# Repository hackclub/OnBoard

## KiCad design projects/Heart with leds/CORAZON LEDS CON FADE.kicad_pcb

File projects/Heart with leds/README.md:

---
name: "Franco Gonzalez Liotta"
slack_handle: "@Franco"
github_handle: "@aGuyWhoHasGithub"
tutorial: # None
---

# Heart with leds(ajustable fade in and fade out frequency and brightness)

<!-- Describe your board in 2-3 sentences. What are you making? What will it do? -->
This  project is basically a heart-shaped form pcb with leds that turn on-off with fade in and fade out effect,
which you can adjust, also the brightness is adjustable.

<!-- How much is it going to cost? -->
10.89 reais of the cost of 5 pcbs(since its cheaper than paying the order with dollars) and 147.97 reais of shipping cost
<!-- Tell us a little bit about your design process. What were some challenges? What helped? ***Totally optional*** -->
Nothing was that complicated, it was very easy for me to be honest...

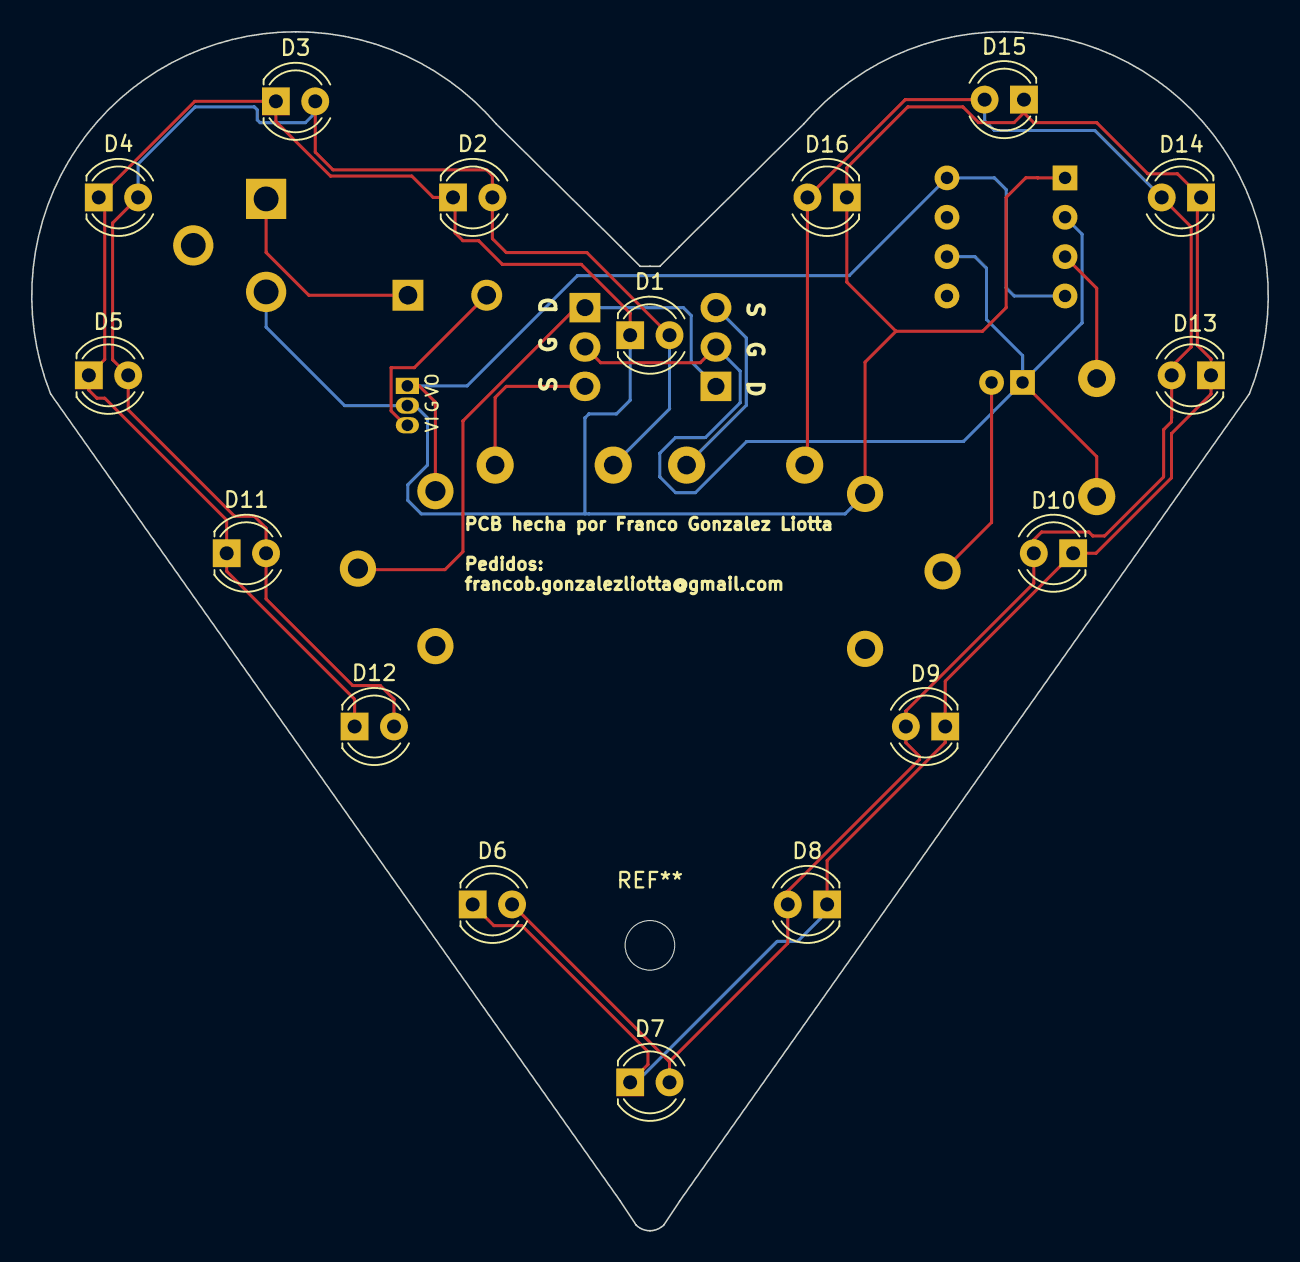
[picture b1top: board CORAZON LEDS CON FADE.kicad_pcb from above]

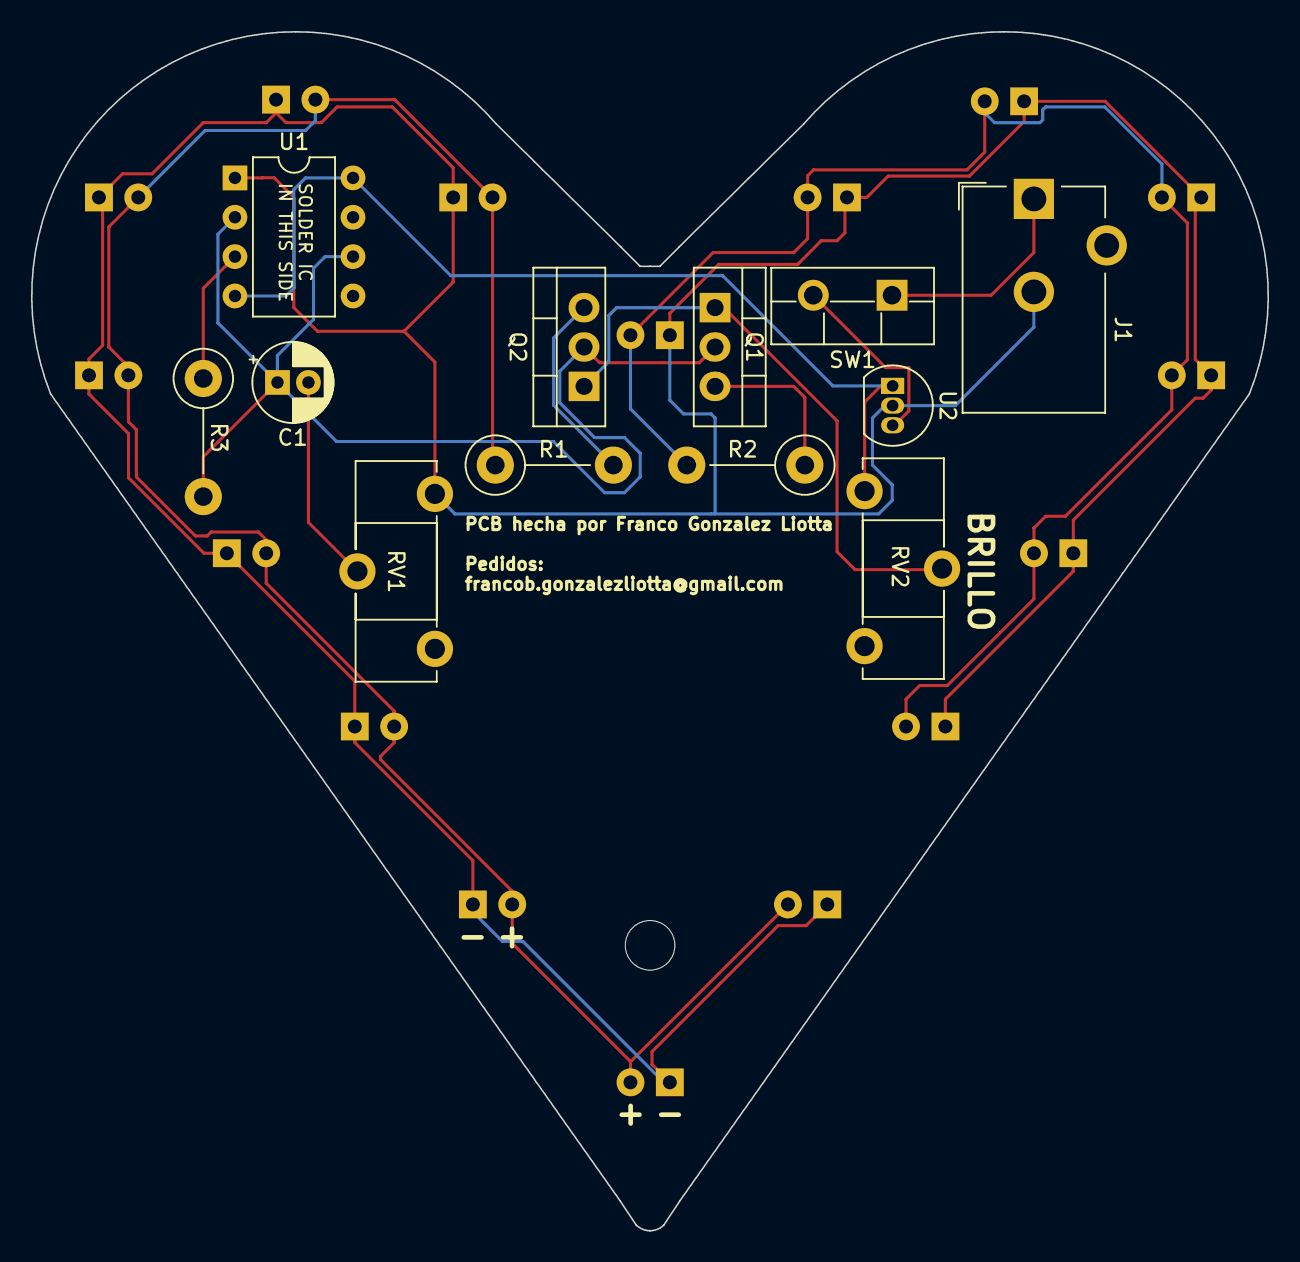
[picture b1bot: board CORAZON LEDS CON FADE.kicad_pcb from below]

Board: 2 copper layers, 79.8 x 77.4 mm, 28 parts (12 on the bottom side), 5 nets.

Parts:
C1: C_Polarized; CP_Radial_D5.0mm_P2.00mm
D1, D2, D3, D4, D5, D6, D7, D8, D9, D10, D11, D12, D13, D14, D15, D16: LED; LED_D4.0mm
J1: Jack-DC; BarrelJack_CUI_PJ-102AH_Horizontal
Q1, Q2: NMOS; TO-220-3_Vertical
R1, R2, R3: R; R_Axial_DIN0411_L9.9mm_D3.6mm_P7.62mm_Vertical
RV1, RV2: R_Potentiometer; Potentiometer_ACP_CA14-H5_Horizontal
SW1: SW_SPST; TO-220F-2_Vertical
U1: NE555P; DIP-8_W7.62mm
U2: L78L05_TO92; TO-92_Inline

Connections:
NET-(J1-VI): J1.1, SW1.1 (A)
unnamed: D1.2 (A), D2.2 (A), D3.2 (A), D4.2 (A), D5.2 (A), D11.2 (A), D12.2 (A), R2.2
unnamed: D6.2 (A), D7.2 (A), D8.2 (A), D9.2 (A), D10.2 (A), D13.2 (A), D14.2 (A), D15.2 (A), D16.2 (A), R1.1
unnamed: SW1.2 (B), U2.3 (VI)
unnamed: RV2.1, U1.4 (R), U1.8 (VCC), U2.1 (VO)

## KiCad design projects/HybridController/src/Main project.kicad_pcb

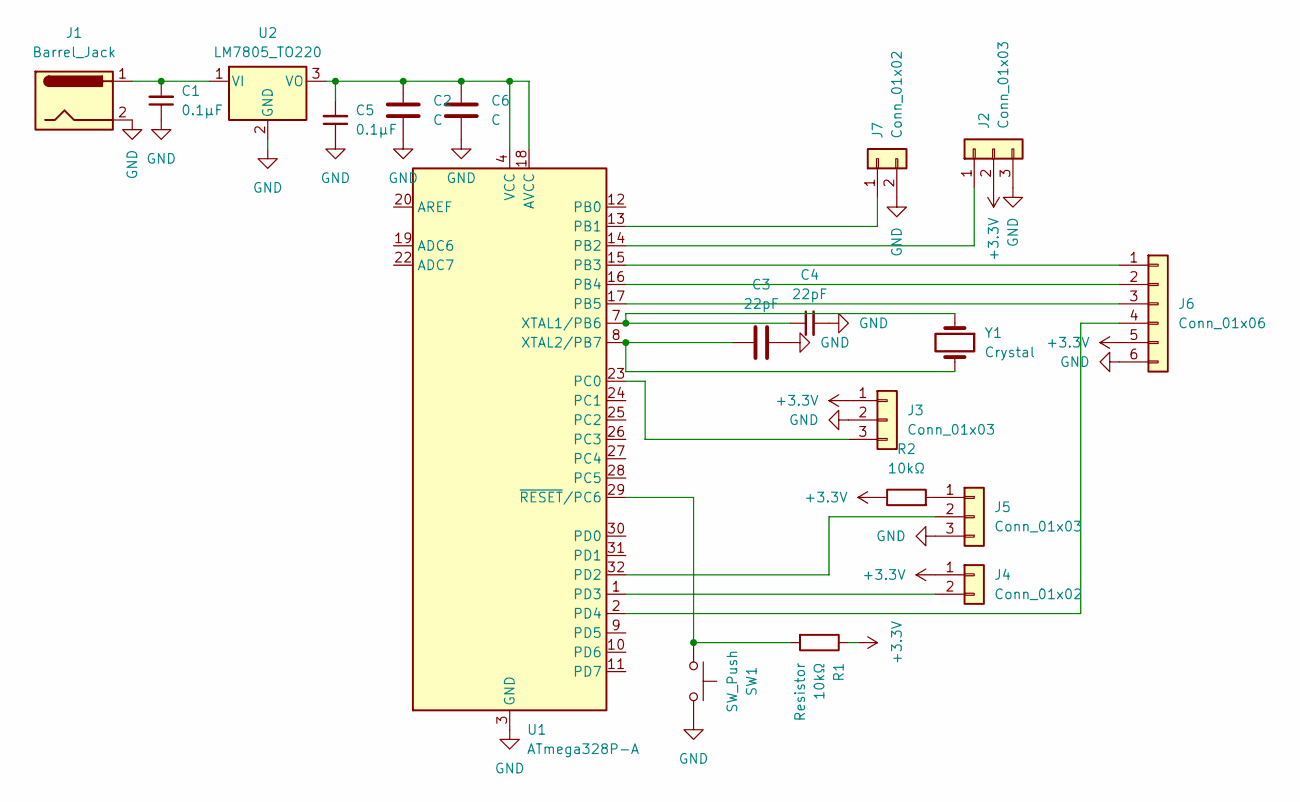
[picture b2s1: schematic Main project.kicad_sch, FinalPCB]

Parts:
C1, C5: 0.1µF; C_0805_2012Metric
C2, C6: C; C_0805_2012Metric
C3, C4: 22pF; C_0805_2012Metric
J1: Barrel_Jack; BarrelJack_SwitchcraftConxall_RAPC10U_Horizontal
J2, J3, J5: Conn_01x03; PinHeader_1x03_P2.54mm_Vertical
J4, J7: Conn_01x02; PinHeader_1x02_P2.54mm_Vertical
J6: Conn_01x06; PinHeader_1x06_P2.54mm_Vertical
R1: 10kΩ; C_0805_2012Metric
R2: 10kΩ; R_0805_2012Metric
SW1: SW_Push; SW_Push_1P1T_NO_6x6mm_H9.5mm
U1: ATmega328P-A; TQFP-32_7x7mm_P0.8mm
U2: LM7805_TO220; TO-220-3_Vertical
Y1: Crystal; Crystal_HC49-U_Vertical

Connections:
+3.3V: J2.2, J3.1, J4.1, J6.5, R1.1, R2.1
GND: C1.1, C2.1, C3.2, C4.2, C5.1, C6.1, J1.2, J2.3, J3.2, J5.3, J6.6, J7.2, SW1.2, U1.3 (GND), U1.5 (GND), U1.21 (GND), U2.2 (GND)
unnamed: J2.1, U1.14 (PB2)
unnamed: J3.3, U1.23 (PC0)
unnamed: J4.2, U1.1 (PD3)
unnamed: J5.1, R2.2
unnamed: J5.2, U1.32 (PD2)
unnamed: J6.1, U1.15 (PB3)
unnamed: J6.2, U1.16 (PB4)
unnamed: J6.3, U1.17 (PB5)
unnamed: J6.4, U1.2 (PD4)
unnamed: J7.1, U1.13 (PB1)
unnamed: C2.2, C5.2, C6.2, U1.4 (VCC), U1.6 (VCC), U1.18 (AVCC), U2.3 (VO)
unnamed: C4.1, U1.7 (XTAL1/PB6), Y1.1
unnamed: C3.1, U1.8 (XTAL2/PB7), Y1.2
unnamed: R1.2, SW1.1, U1.29 (~RESET/PC6)
unnamed: C1.2, J1.1, U2.1 (VI)

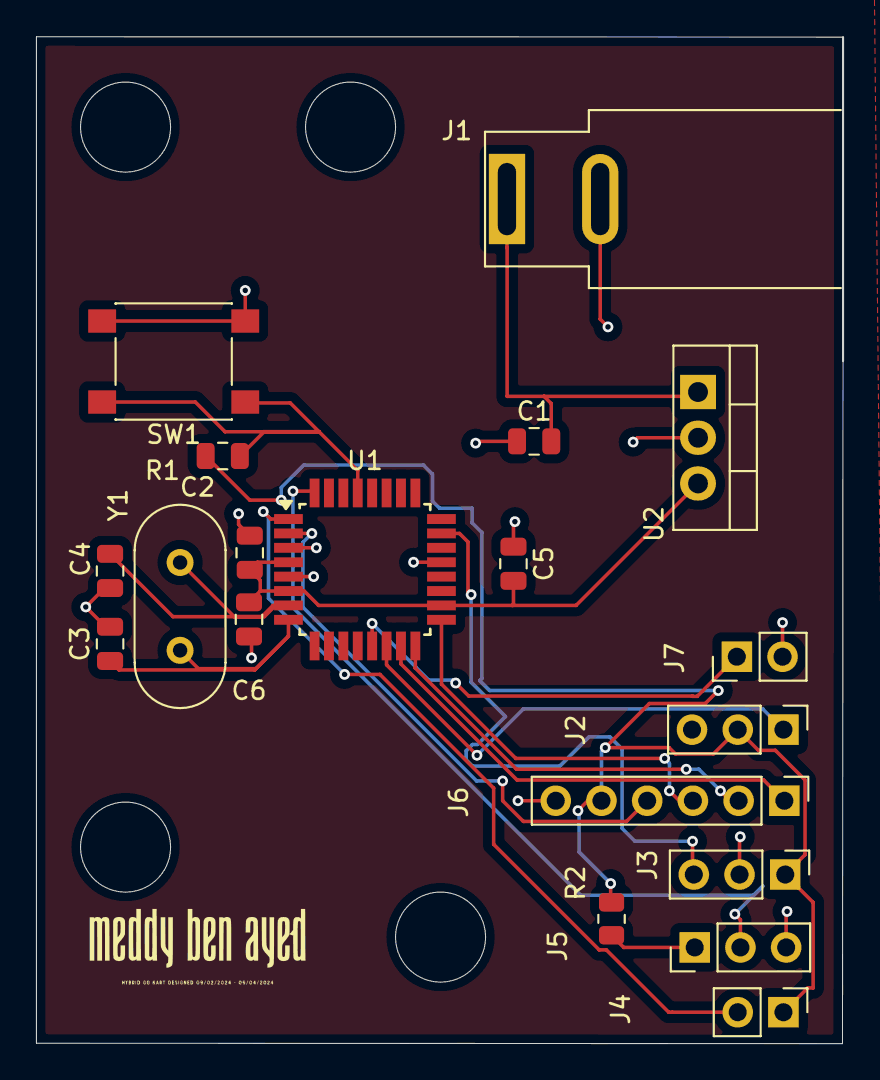
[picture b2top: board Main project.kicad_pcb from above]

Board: 4 copper layers, 44.8 x 55.9 mm, 20 parts (0 on the bottom side), 17 nets.

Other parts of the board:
 : logo

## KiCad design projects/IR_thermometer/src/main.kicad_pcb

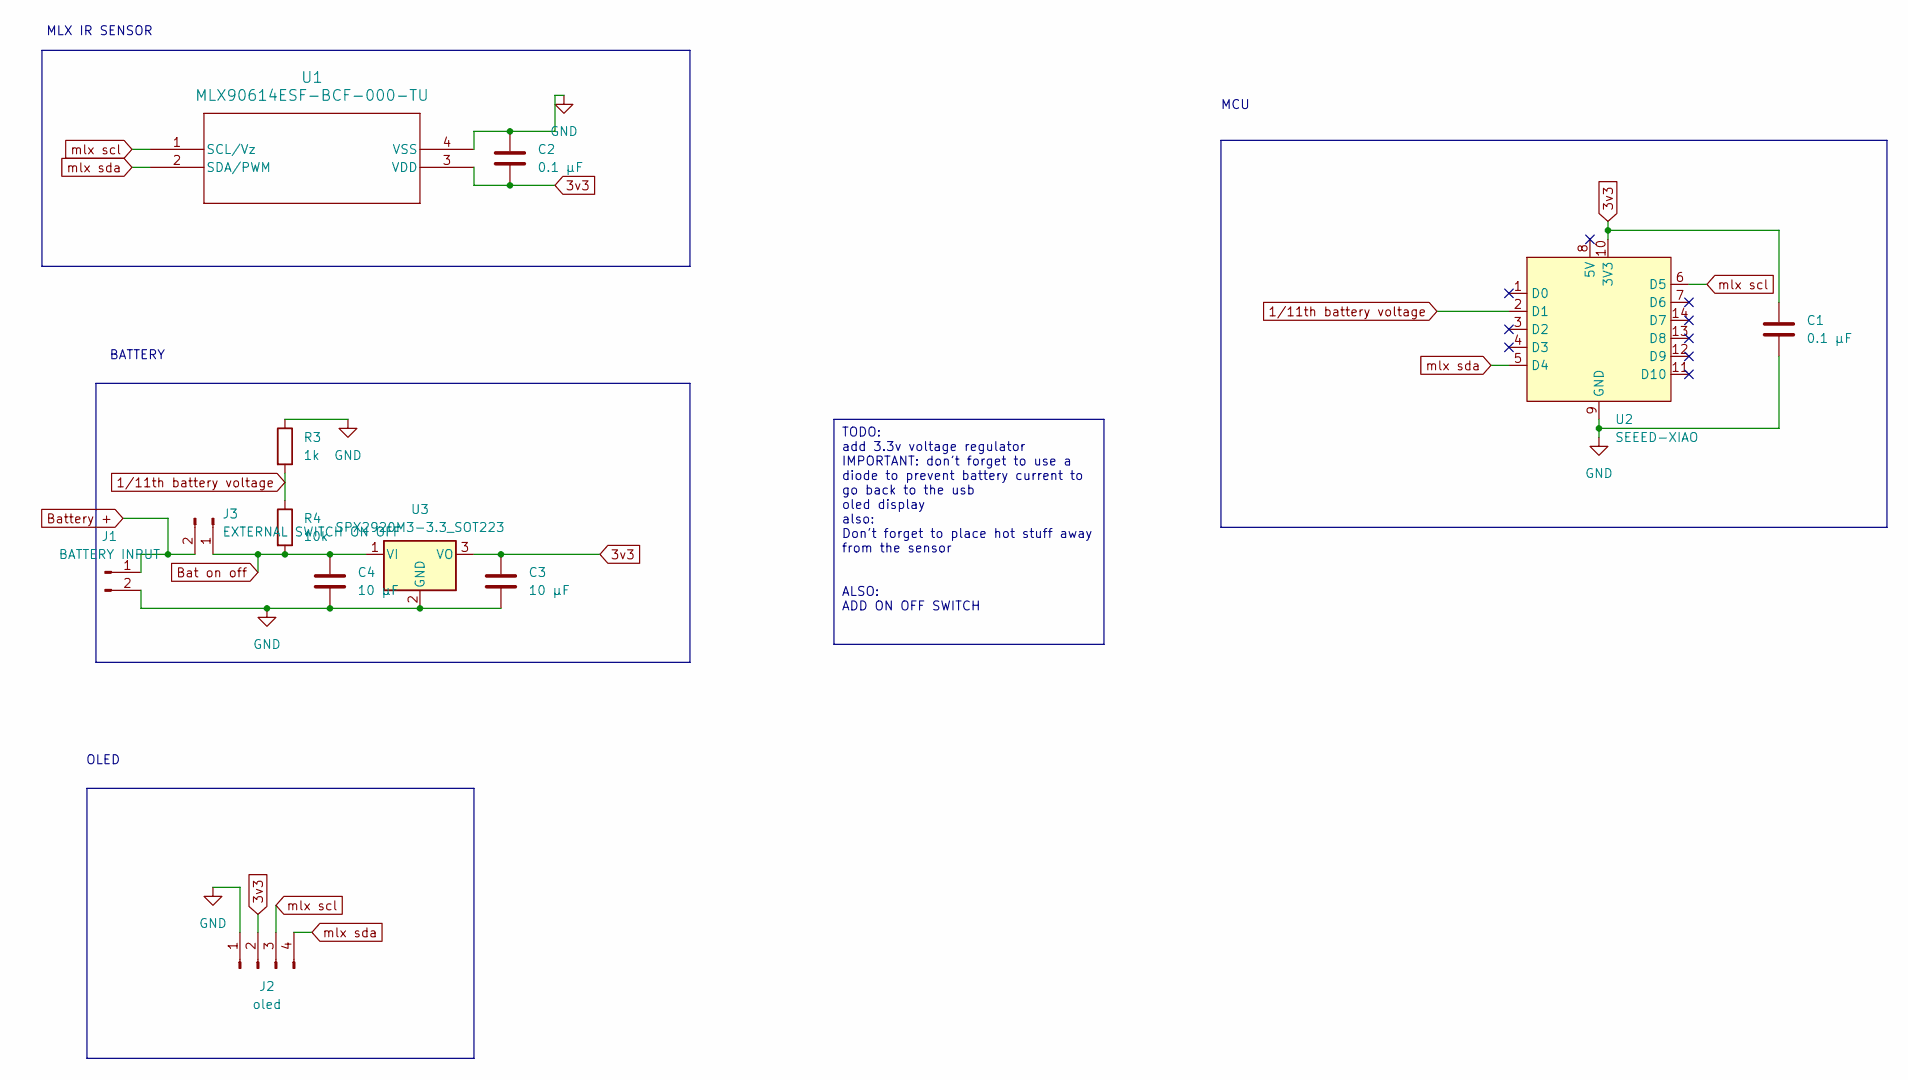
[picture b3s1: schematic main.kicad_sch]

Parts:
C1, C2: 0.1 µF; C_0805_2012Metric_Pad1.18x1.45mm_HandSolder
C3, C4: 10 µF; C_0805_2012Metric_Pad1.18x1.45mm_HandSolder
J1: BATTERY INPUT; PinHeader_1x02_P2.54mm_Vertical
J2: oled; PinHeader_1x04_P2.54mm_Vertical
J3: EXTERNAL SWITCH ON OFF; PinHeader_1x02_P2.54mm_Vertical
R3: 1k; R_0805_2012Metric_Pad1.20x1.40mm_HandSolder
R4: 10k; R_0805_2012Metric_Pad1.20x1.40mm_HandSolder
U1: MLX90614ESF-BCF-000-TU; MLX90614xCF_MEL
U2: SEEED-XIAO; XIAO-14P-THT-2.54-21x17.8MM
U3: SPX2920M3-3.3_SOT223; SOT-223-3_TabPin2

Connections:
1/11th battery voltage: R3.2, R4.1, U2.2 (D1)
3v3: C1.1, C2.2, C3.1, J2.2, U1.3 (VDD), U2.10 (3V3), U3.3 (VO)
Bat on off: C4.1, J3.1, R4.2, U3.1 (VI)
Battery +: J1.1, J3.2
GND: C1.2, C2.1, C3.2, C4.2, J1.2, J2.1, R3.1, U1.4 (VSS), U2.9 (GND), U3.2 (GND)
mlx scl: J2.3, U1.1 (SCL/Vz), U2.6 (D5)
mlx sda: J2.4, U1.2 (SDA/PWM), U2.5 (D4)

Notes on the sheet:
TODO: add 3.3v voltage regulator IMPORTANT: don't forget to use a diode to prevent battery current to go back to the usb oled display also: Don't forget to place hot stuff away from the sensor ALSO: ADD ON OFF SWITCH
MLX IR SENSOR
BATTERY
OLED
MCU

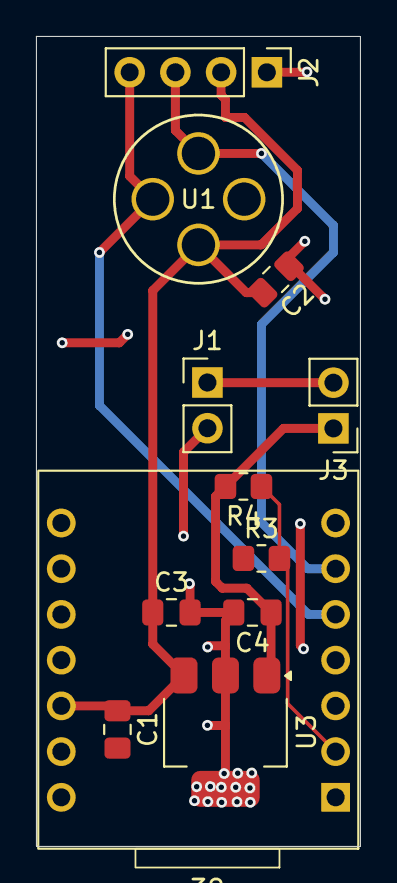
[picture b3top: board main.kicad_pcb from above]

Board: 2 copper layers, 18.0 x 45.0 mm, 12 parts (0 on the bottom side), 7 nets.

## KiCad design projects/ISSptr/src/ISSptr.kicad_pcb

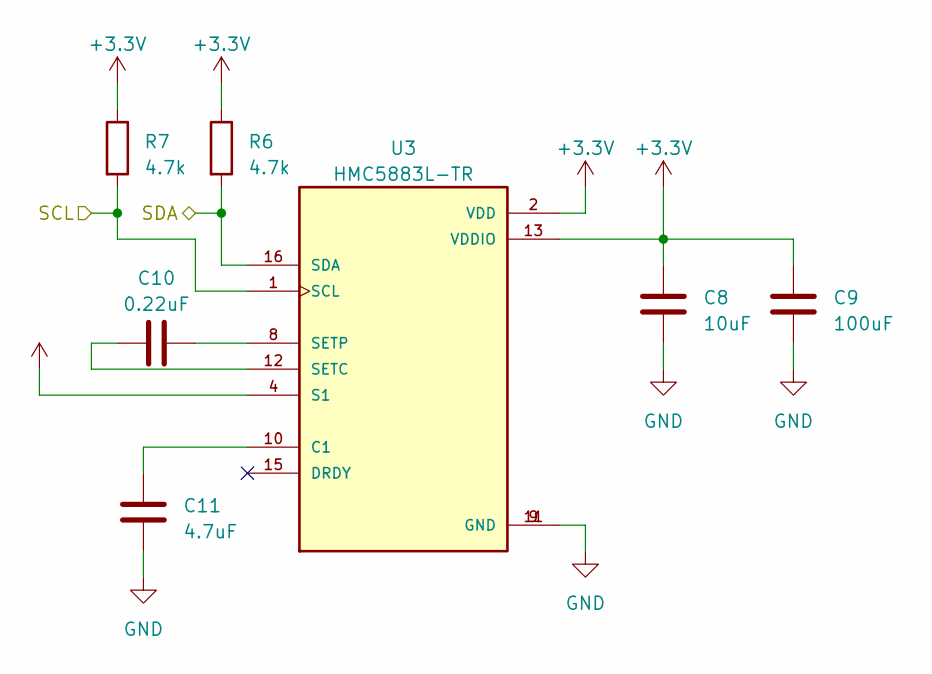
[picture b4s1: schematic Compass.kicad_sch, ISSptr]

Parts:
C8: 10uF; C_0603_1608Metric; LCSC C19702
C9: 100uF; C_0603_1608Metric; LCSC C730416
C10: 0.22uF; C_0603_1608Metric; LCSC C472764
C11: 4.7uF; C_0603_1608Metric; LCSC C307469
R6, R7: 4.7k; R_0603_1608Metric; LCSC C23162
U3: HMC5883L-TR; XDCR_HMC5883L-TR; PARTREV E; LCSC C976032

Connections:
+3.3V: C8.1, C9.1, R6.1, R7.1, U3.2 (VDD), U3.4 (S1), U3.13 (VDDIO); also elsewhere on the board
/Compass/SCL: R7.2, U3.1 (SCL); also elsewhere on the board
/Compass/SDA: R6.2, U3.16 (SDA); also elsewhere on the board
GND: C8.2, C9.2, C11.1, U3.9 (GND), U3.11 (GND); also elsewhere on the board
unnamed: C11.2, U3.10 (C1)
unnamed: C10.1, U3.12 (SETC)
unnamed: C10.2, U3.8 (SETP)

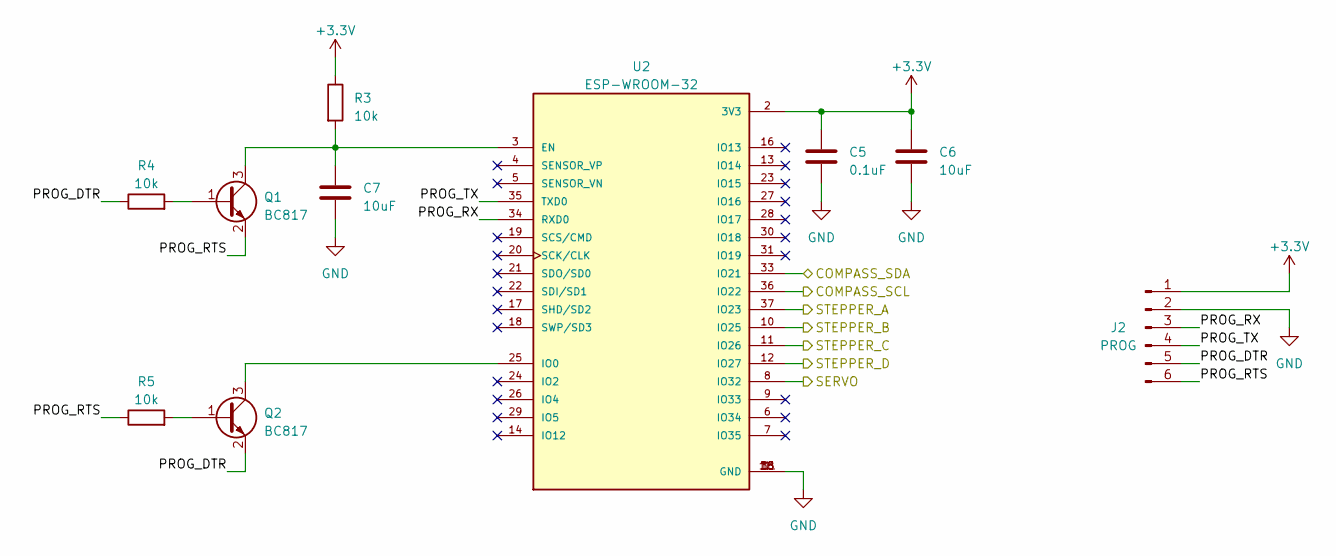
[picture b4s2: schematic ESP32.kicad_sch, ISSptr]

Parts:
C5: 0.1uF; C_0603_1608Metric; LCSC C1591
C6, C7: 10uF; C_0603_1608Metric; LCSC C19702
J2: PROG; PinHeader_1x06_P2.54mm_Vertical
Q1, Q2: BC817; SOT-23; LCSC C475629
R3, R4, R5: 10k; R_0603_1608Metric; LCSC C25804
U2: ESP-WROOM-32; MODULE_ESP-WROOM-32; LCSC C82899

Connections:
+3.3V: C5.1, C6.1, J2.1, R3.1, U2.2 (3V3); also elsewhere on the board
/Compass/SCL: U2.36 (IO22); also elsewhere on the board
/Compass/SDA: U2.33 (IO21); also elsewhere on the board
/ESP32/PROG_DTR: J2.5, Q2.2 (E), R4.1
/ESP32/PROG_RTS: J2.6, Q1.2 (E), R5.1
/ESP32/PROG_RX: J2.3, U2.34 (RXD0)
/ESP32/PROG_TX: J2.4, U2.35 (TXD0)
/ESP32/SERVO: U2.8 (IO32); also elsewhere on the board
/ESP32/STEPPER_A: U2.37 (IO23); also elsewhere on the board
/ESP32/STEPPER_B: U2.10 (IO25); also elsewhere on the board
/ESP32/STEPPER_C: U2.11 (IO26); also elsewhere on the board
/ESP32/STEPPER_D: U2.12 (IO27); also elsewhere on the board
GND: C5.2, C6.2, C7.2, J2.2, U2.1 (GND), U2.1.1 (GND), U2.15 (GND), U2.38 (GND); also elsewhere on the board
unnamed: Q1.1 (B), R4.2
unnamed: C7.1, Q1.3 (C), R3.2, U2.3 (EN)
unnamed: Q2.1 (B), R5.2
unnamed: Q2.3 (C), U2.25 (IO0)

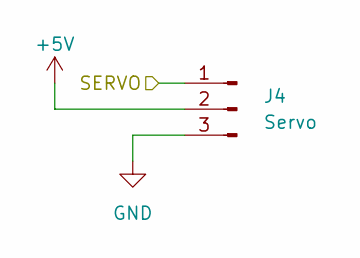
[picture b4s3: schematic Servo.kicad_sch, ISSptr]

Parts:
J4: Servo; PinHeader_1x03_P2.54mm_Horizontal

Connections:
+5V: J4.2; also elsewhere on the board
/ESP32/SERVO: J4.1; also elsewhere on the board
GND: J4.3; also elsewhere on the board

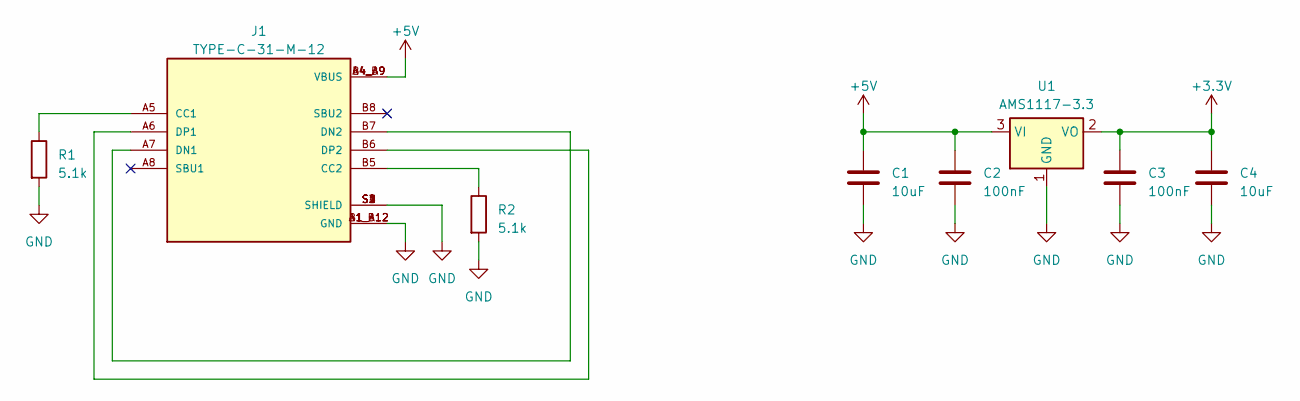
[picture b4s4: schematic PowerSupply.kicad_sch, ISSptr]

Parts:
C1, C4: 10uF; C_0603_1608Metric; LCSC C19702
C2, C3: 100nF; C_0603_1608Metric; LCSC C1591
J1: TYPE-C-31-M-12; HRO_TYPE-C-31-M-12; PARTREV 2020.12.08; LCSC C165948
R1, R2: 5.1k; R_0603_1608Metric; LCSC C23186
U1: AMS1117-3.3; SOT-223-3_TabPin2; LCSC C6186

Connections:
+3.3V: C3.1, C4.1, U1.2 (VO); also elsewhere on the board
+5V: C1.1, C2.1, J1.A4_B9 (VBUS), J1.B4_A9 (VBUS), U1.3 (VI); also elsewhere on the board
GND: C1.2, C2.2, C3.2, C4.2, J1.A1_B12 (GND), J1.B1_A12 (GND), J1.S1 (SHIELD), J1.S2 (SHIELD), J1.S3 (SHIELD), J1.S4 (SHIELD), R1.2, R2.2, U1.1 (GND); also elsewhere on the board
unnamed: J1.A5 (CC1), R1.1
unnamed: J1.B5 (CC2), R2.1
unnamed: J1.A7 (DN1), J1.B7 (DN2)
unnamed: J1.A6 (DP1), J1.B6 (DP2)

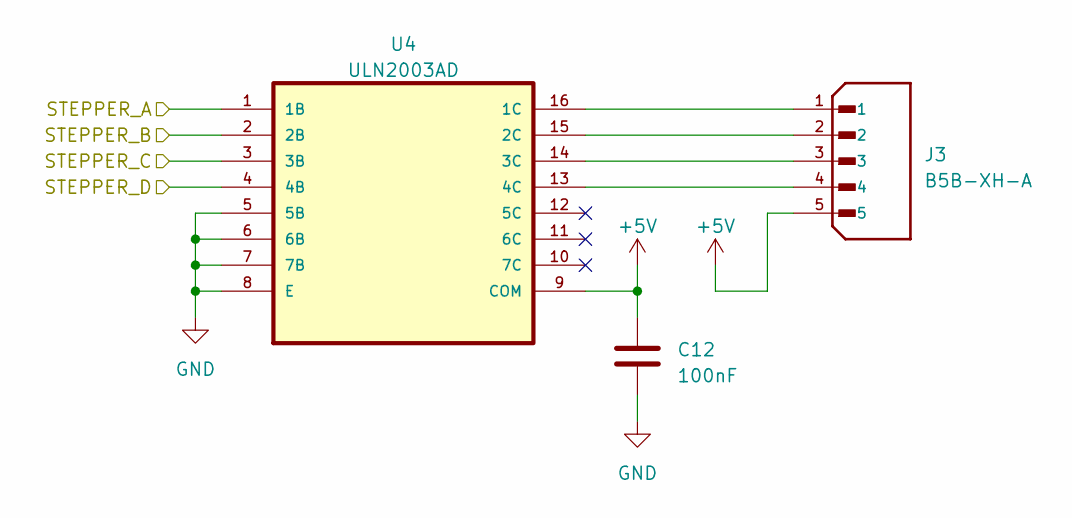
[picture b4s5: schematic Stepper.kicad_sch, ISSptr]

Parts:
C12: 100nF; C_0603_1608Metric; LCSC C1591
J3: B5B-XH-A; JST_B5B-XH-A_LF__SN_; PARTREV 7/4/21; LCSC C157991
U4: ULN2003AD; SOIC127P600X175-16N; LCSC C908113

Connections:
+5V: C12.1, J3.5, U4.9 (COM); also elsewhere on the board
/ESP32/STEPPER_A: U4.1 (1B); also elsewhere on the board
/ESP32/STEPPER_B: U4.2 (2B); also elsewhere on the board
/ESP32/STEPPER_C: U4.3 (3B); also elsewhere on the board
/ESP32/STEPPER_D: U4.4 (4B); also elsewhere on the board
GND: C12.2, U4.5 (5B), U4.6 (6B), U4.7 (7B), U4.8 (E); also elsewhere on the board
unnamed: J3.1, U4.16 (1C)
unnamed: J3.2, U4.15 (2C)
unnamed: J3.3, U4.14 (3C)
unnamed: J3.4, U4.13 (4C)

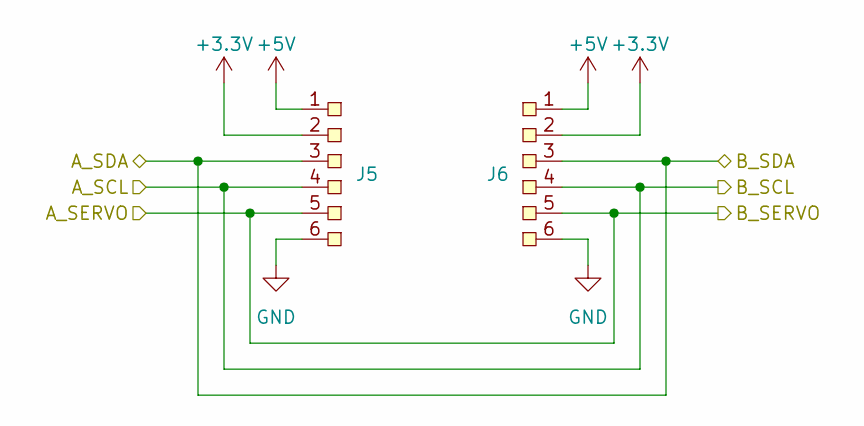
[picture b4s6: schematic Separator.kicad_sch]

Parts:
J5, J6: SolderPad-6pin

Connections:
+3.3V: J5.2, J6.2; also elsewhere on the board
+5V: J5.1, J6.1; also elsewhere on the board
/Compass/SCL: J5.4, J6.4; also elsewhere on the board
/Compass/SDA: J5.3, J6.3; also elsewhere on the board
/ESP32/SERVO: J5.5, J6.5; also elsewhere on the board
GND: J5.6, J6.6; also elsewhere on the board

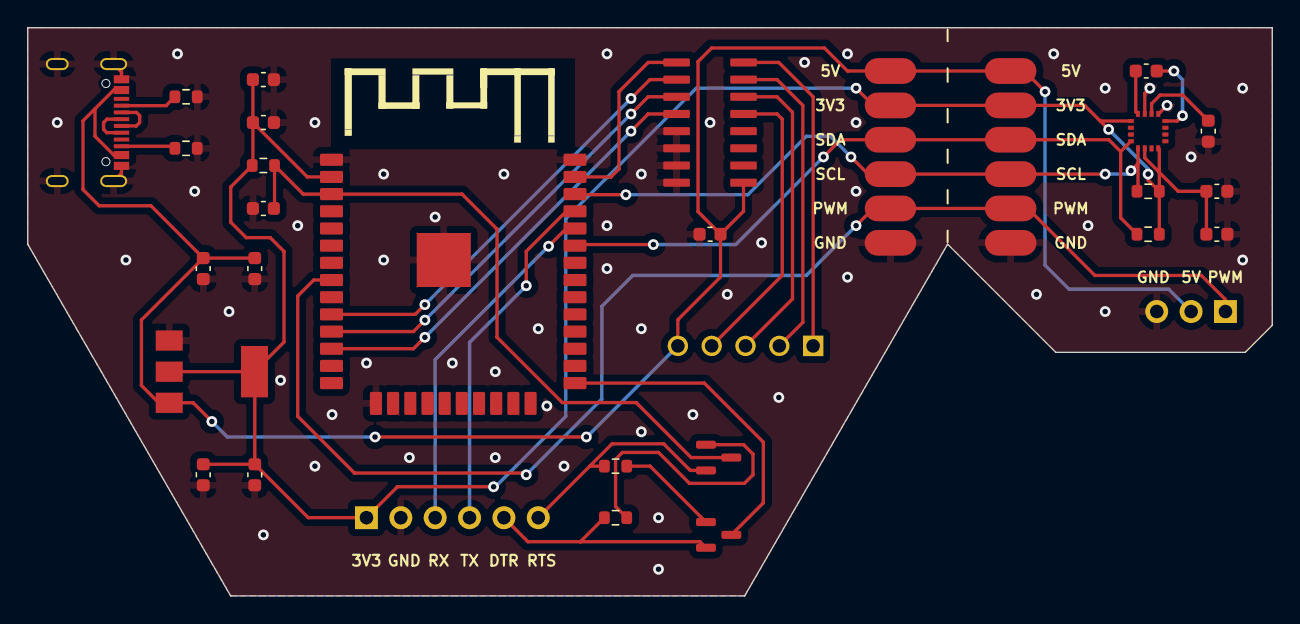
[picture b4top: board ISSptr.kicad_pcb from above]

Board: 2 copper layers, 92.0 x 42.0 mm, 31 parts (0 on the bottom side), 29 nets.

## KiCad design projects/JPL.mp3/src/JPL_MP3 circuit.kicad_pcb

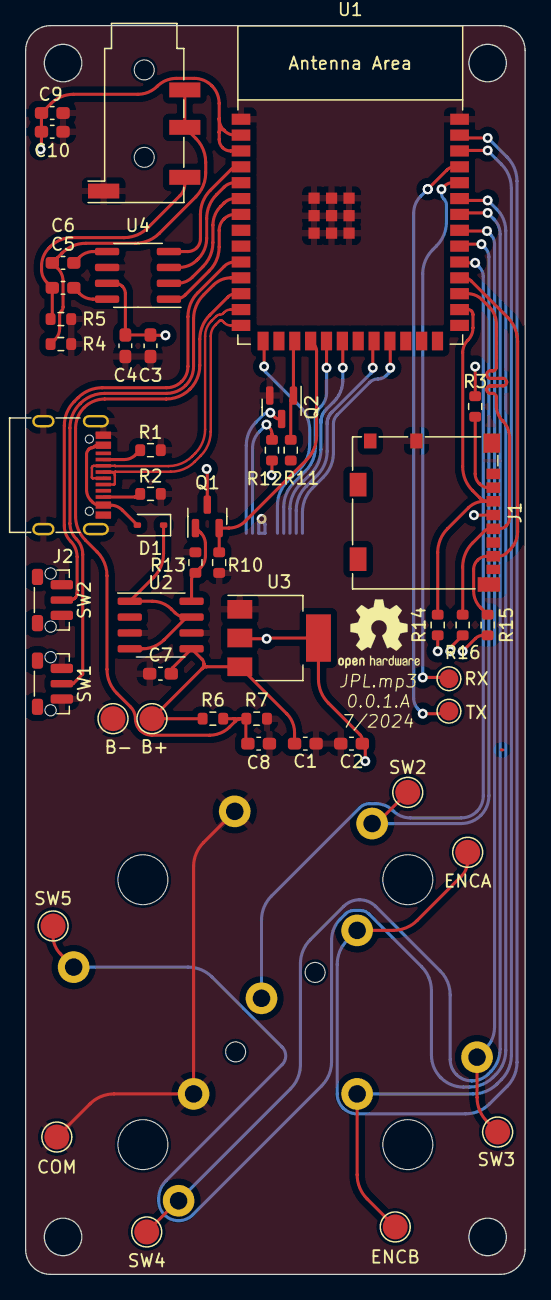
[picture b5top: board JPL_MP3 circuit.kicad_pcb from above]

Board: 4 copper layers, 40.0 x 100.0 mm, 48 parts (1 on the bottom side), 43 nets.

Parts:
B+: B+; TestPoint_Pad_D2.0mm
B-: B-; TestPoint_Pad_D2.0mm
C1, C2: 10uF; C_0603_1608Metric_Pad1.08x0.95mm_HandSolder
C3: 1uF; C_0603_1608Metric_Pad1.08x0.95mm_HandSolder
C4: 0.1uF; C_0603_1608Metric_Pad1.08x0.95mm_HandSolder
C5, C6: 10 uF; C_0603_1608Metric_Pad1.08x0.95mm_HandSolder
C7: 2.2 uF; C_0603_1608Metric_Pad1.08x0.95mm_HandSolder
C8: 10 nF; C_0603_1608Metric_Pad1.08x0.95mm_HandSolder
C9, C10: .1uF; C_0603_1608Metric_Pad1.08x0.95mm_HandSolder
COM: TestPoint_Pad_D2.0mm
D1: 1N5819WS; D_SOD-323
ENCA: TestPoint_Pad_D2.0mm
ENCB: TestPoint_Pad_D2.0mm
Enc1: ANO Rotary Encoder
J1: Micro_SD_Card; microSD_HC_Molex_104031-0811
J2: USB_C; USB_C_Receptacle_G-Switch_GT-USB-7010ASV
J4: Conn_01x12; TE_1-1734839-2_1x12-1MP_P0.5mm_Horizontal
Q1, Q2: BSS138; SOT-23
R1, R2: 5.1K; R_0603_1608Metric
R3, R4, R5, R10, R11, R13, R14, R15, R16: 10K; R_0603_1608Metric
R6, R7: 100K; R_0603_1608Metric
R12: 10; R_0603_1608Metric
RX: TestPoint_Pad_D1.5mm
SW1, SW2#2: SW_Push; SW_Push_1P1T-MP_NO_Horizontal_Alps_SKRTLAE010
SW2, SW3, SW4, SW5: TestPoint_Pad_D2.0mm
TX: TestPoint_Pad_D1.5mm
U1: ESP32-S3-WROOM-1
U2: MAX1811; SOIC-8_3.9x4.9mm_P1.27mm
U3: AMS1117-3.3; SOT-223-3_TabPin2
U4: SOIC-8_3.9x4.9mm_P1.27mm

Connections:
+3.3V: C2.1, C3.1, C4.1, C9.1, C10.1, J1.4 (VDD), J4.8, J4.9, Q1.3 (D), R3.1, R12.1, R14.1, R15.2, R16.2, U1.2 (3V3), U1.3 (EN), U3.2 (VO), U4.7 (VDD)
+5V: D1.1 (K), U2.1 (SELV), U2.4 (IN), U2.7 (EN)
AUDIO_LEFT: C5.2, R5.1
AUDIO_RIGHT: C6.1, R4.1
BACKLIGHT: Q2.1 (G), R11.1, U1.17 (GPIO9/TOUCH9/ADC1_CH8/FSPIHD/SUBSPIHD)
BAT_SENSE: C8.2, R6.2, R7.1, U1.12 (GPIO8/TOUCH8/ADC1_CH7/SUBSPICS1)
CHG: Q1.2 (S), R10.1, U1.18 (GPIO10/TOUCH10/ADC1_CH9/FSPICS0/FSPIIO4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)
DAC_MCLK: U1.4 (GPIO4/TOUCH4/ADC1_CH3), U4.4 (MCLK)
ENCA: ENCA.1, Enc1.A, U1.39 (GPIO1/TOUCH1/ADC1_CH0)
ENCB: ENCB.1, Enc1.B, U1.38 (GPIO2/TOUCH2/ADC1_CH1)
GND: B-.1, C1.2, C2.2, C3.2, C4.2, C7.2, C8.1, C9.2, C10.2, COM.1, Enc1.COM_A, Enc1.COM_B, J1.6 (VSS), J1.9 (SHIELD), J2.A1 (GND), J2.A12 (GND), J2.B1 (GND), J2.B12 (GND), J2.S1 (SHIELD), J4.1, J4.12, Q2.2 (S), R1.2, R2.2, R4.2, R5.2, R7.2, R10.2, R11.2, R13.2, SW1.1, SW2#2.1, U1.1 (GND), U1.40 (GND), U1.41 (GND), U2.3 (GND), U2.6 (GND), U3.1 (GND), U4.6 (GND)
I2S_LRCLK: U1.5 (GPIO5/TOUCH5/ADC1_CH4), U4.3 (LRCK)
I2S_SCLK: U1.6 (GPIO6/TOUCH6/ADC1_CH5), U4.2 (DEM/SCLK)
I2S_SD: U1.7 (GPIO7/TOUCH7/ADC1_CH6), U4.1 (SDIN)
unnamed: B+.1, C1.1, C7.1, R6.1, U2.5 (BATT), U3.3 (VI)
unnamed: D1.2 (A), J2.A4 (VBUS), J2.A9 (VBUS), J2.B4 (VBUS), J2.B9 (VBUS)
unnamed: J1.2 (DAT3/CD), R3.2
unnamed: J2.A5 (CC1), R1.1
unnamed: J2.B5 (CC2), R2.1
unnamed: J4.10, R12.2
unnamed: J4.11, Q2.3 (D)
unnamed: Q1.1 (G), R13.1, U2.8 (~CHG)
unnamed: C5.1, U4.8 (AOUTL)
unnamed: C6.2, U4.5 (AOUTR)
SD_CLK: J1.5 (CLK), R16.1, U1.29 (SPIIO7/GPIO36/FSPICLK/SUBSPICLK)
SD_CMD: J1.3 (CMD), R14.2, U1.28 (SPIIO6/GPIO35/FSPID/SUBSPID)
SD_D0: J1.7 (DAT0), R15.1, U1.30 (SPIDQS/GPIO37/FSPIQ/SUBSPIQ)
SW1: Enc1.S1, U1.31 (GPIO38/FSPIWP/SUBSPIWP)
SW2: Enc1.S2, SW2.1, U1.32 (MTCK/GPIO39/CLK_OUT3/SUBSPICS1)
SW3: Enc1.S3, SW3.1, U1.33 (MTDO/GPIO40/CLK_OUT2)
SW4: Enc1.S4, SW4.1, U1.34 (MTDI/GPIO41/CLK_OUT1)
SW5: Enc1.S5, SW5.1, U1.35 (MTMS/GPIO42)
TFT_CS: J4.2, U1.23 (GPIO21)
TFT_DC: J4.3, U1.22 (GPIO14/TOUCH14/ADC2_CH3/FSPIWP/FSPIDQS/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)
TFT_RST: J4.6, U1.15 (GPIO3/TOUCH3/ADC1_CH2)
TFT_SCLK: J4.4, U1.20 (GPIO12/TOUCH12/ADC2_CH1/FSPICLK/FSPIIO6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)
TFT_SDA: J4.5, U1.19 (GPIO11/TOUCH11/ADC2_CH0/FSPID/FSPIIO5/S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)
UART_RX: RX.1, U1.36 (U0RXD/GPIO44/CLK_OUT2)
UART_TX: TX.1, U1.37 (U0TXD/GPIO43/CLK_OUT1)
USB_D+: J2.A6 (D+), J2.B6 (D+), U1.14 (GPIO20/U1CTS/ADC2_CH9/CLK_OUT1/USB_D+)
USB_D-: J2.A7 (D-), J2.B7 (D-), U1.13 (GPIO19/U1RTS/ADC2_CH8/CLK_OUT2/USB_D-)
VOL_DOWN: SW1.2, U1.11 (GPIO18/U1RXD/ADC2_CH7/CLK_OUT3)
VOL_UP: SW2#2.2, U1.10 (GPIO17/U1TXD/ADC2_CH6)
